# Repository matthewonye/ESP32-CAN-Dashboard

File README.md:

# ESP32-CAN-Dashboard
An embedded systems project that uses ESP32 microcontrollers and CAN bus communication to simulate, transmit, receive, and display vehicle data in real time.

The project combines C++ firmware, CAN communication, MATLAB/Simulink modeling, and custom PCB design to demonstrate hardware/software integration for automotive electronics.

# Project Overview
The system uses two ESP32 microcontrollers connected through SN65HVD230 CAN transceivers.

* Transmitter (Simulated Vehicle): Generates vehicle data, including engine RPM, speed, and coolant temperature, and transmits it over CAN.

* Receiver (Dashboard): Receives and decodes CAN messages and displays the vehicle data on a 128×64 OLED screen.

A custom PCB was designed in KiCad to integrate the dashboard ESP32, CAN interface, OLED connections, power regulation, and external CAN connections.

# Hardware Components
* 2 ESP32-WROOM-32 development boards (bench testing)

* SN65HVD230 CAN transceiver modules

* SSD1306 128×64 OLED display

* MP1584EN adjustable buck converter module (for PCB assembly)

* Custom designed PCB

* 120 Ω CAN termination resistor and jumper

* Screw terminals, headers, and supporting passive components

# Tech/Tools Used:

* Programming      |     C/C++, Arduino IDE

* Microcontrollers   |   ESP32

* Communication     |    CAN Bus, ESP32 TWAI

* PCB Design      |      KiCad

* Simulation      |     MATLAB/Simulink

* Interfaces     |       OLED

* Debugging       |     Serial Monitor, Multimeter

# System Architecture

Simulated Vehicle ESP32 → SN65HVD230 → CAN Bus → SN65HVD230 → Dashboard ESP32 → OLED Display

The transmitter generates simulated vehicle signals and packages them into CAN messages. The receiver reconstructs the transmitted values and updates the OLED display.

# CAN Communication

The system uses the ESP32's built-in TWAI controller with external SN65HVD230 transceivers.

CAN Configuration

* Bit rate: 500 kbps
* CAN message ID: 0x100
* Payload length: 5 bytes

Byte/Data

* 0 | RPM High

* 1 | RPM Low

* 2 | Vehicle Speed

* 3 | Coolant Temp

* 4 | Reserved

where RPM is encoded as a 16-bit value and reconstructed by the receiver using bitwise operations.

# [MATLAB/Simulink](https://github.com/matthewonye/ESP32-CAN-Dashboard/tree/main/Simulink)

Developed a Simulink model to simulate vehicle signals and demonstrate CAN payload encoding and decoding.

The model includes:

* Simulated RPM, speed, and coolant temperature signals
* Signal saturation and data-type conversion
* High-byte/low-byte encoding
* Byte-level payload construction
* Decoding and reconstruction of transmitted values

The Simulink model validates the data processing logic; physical CAN communication is handled by the ESP32 hardware and firmware.

# [Custom PCB Design](https://github.com/matthewonye/ESP32-CAN-Dashboard/tree/main/PCB/KiCAD/CAN_Dashboard_PCB)

Designed a multi layer PCB in KiCad to integrate the dashboard hardware into a single assembly.

PCB features:
* ESP32 DevKit footprint

* SN65HVD230 module interface

* OLED connector

* External CANH/CANL/GND connector

* Buck-converter power section

* Switchable 120 Ω CAN termination

* Power indicator LED

* Signal and power test points

* Ground copper plane

* ESP32 antenna copper keepout

# Testing and Validation
* Established CAN communication between two ESP32 development boards

* Verified message transmission and reception

* Decoded vehicle data and displayed it on the OLED

* Validated signal encoding and decoding in MATLAB/Simulink

* Completed KiCad electrical and PCB design-rule checks

# Future Additions 
* Integrate an Assembly routine for low-level data processing

* Add vehicle-data logging capabilities

* Expand dashboard visualization

* Evaluate a protected, listen-only interface for real vehicle CAN networks

# Author
Matthew Onye

Computer Engineering | University of Michigan–Dearborn

[LinkedIn](https://www.linkedin.com/in/matthew-onye-9a4964316/?isSelfProfile=true)

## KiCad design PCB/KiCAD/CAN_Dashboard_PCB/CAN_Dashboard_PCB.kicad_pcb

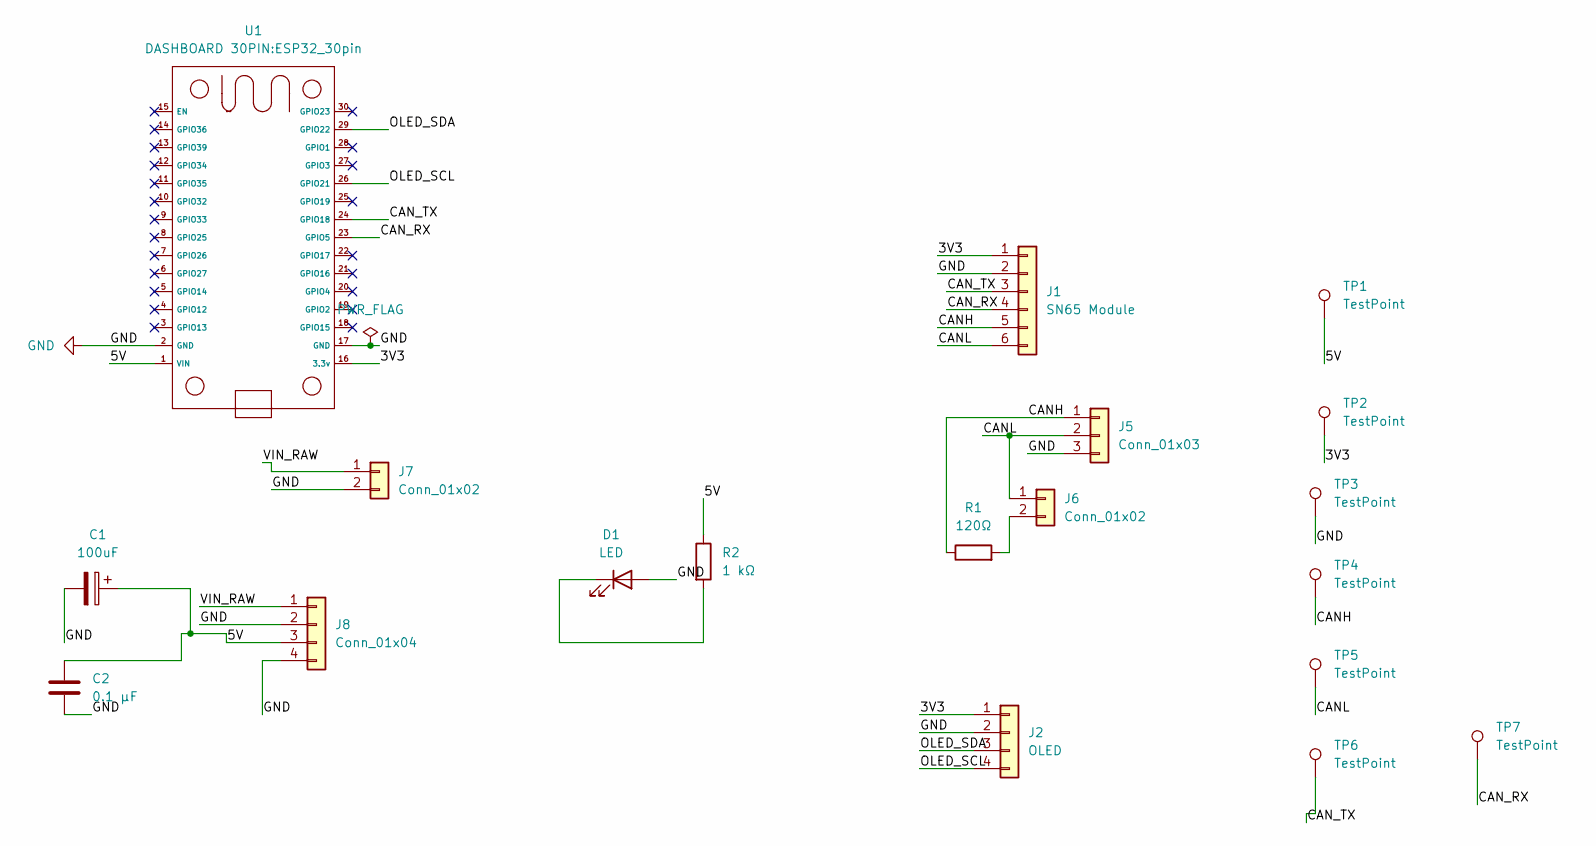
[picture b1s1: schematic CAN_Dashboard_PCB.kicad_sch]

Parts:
C1: 100uF; CP_Radial_D6.3mm_P2.50mm
C2: 0.1 µF; C_Disc_D5.0mm_W2.5mm_P5.00mm
D1: LED; LED_D5.0mm
J1: SN65 Module; PinHeader_1x06_P2.54mm_Vertical
J2: OLED; FanPinHeader_1x04_P2.54mm_Vertical
J5: Conn_01x03; TerminalBlock_Phoenix_MKDS-1,5-3-5.08_1x03_P5.08mm_Horizont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
J6: Conn_01x02; PinHeader_1x02_P2.54mm_Vertical
J7: Conn_01x02; TerminalBlock_Phoenix_MKDS-1,5-2-5.08_1x02_P5.08mm_Horizont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
J8: Conn_01x04; MP1584EN_Mini_Module
R1: 120Ω; R_Axial_DIN0207_L6.3mm_D2.5mm_P10.16mm_Horizontal
R2: 1 kΩ; R_Axial_DIN0207_L6.3mm_D2.5mm_P10.16mm_Horizontal
TP1, TP2, TP3, TP4, TP5, TP6, TP7: TestPoint; TestPoint_THTPad_D2.0mm_Drill1.0mm
U1: ESP32_30pin

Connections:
/3V3: J1.1, J2.1, TP2.1 (1_1), U1.16 (3.3v)
/5V: C1.1, C2.1, J8.3, R2.1, TP1.1 (1_1), U1.1 (VIN)
/CANH: J1.5, J5.1, R1.1, TP4.1 (1_1)
/CANL: J1.6, J5.2, J6.1, TP5.1 (1_1)
/CAN_RX: J1.4, TP7.1 (1_1), U1.23 (GPIO5)
/CAN_TX: J1.3, TP6.1 (1_1), U1.24 (GPIO18)
/OLED_SCL: J2.4, U1.26 (GPIO21)
/OLED_SDA: J2.3, U1.29 (GPIO22)
/VIN_RAW: J7.1, J8.1
GND: C1.2, C2.2, D1.2 (A), J1.2, J2.2, J5.3, J7.2, J8.2, J8.4, TP3.1 (1_1), U1.2 (GND), U1.17 (GND)
unnamed: D1.1 (K), R2.2
unnamed: J6.2, R1.2

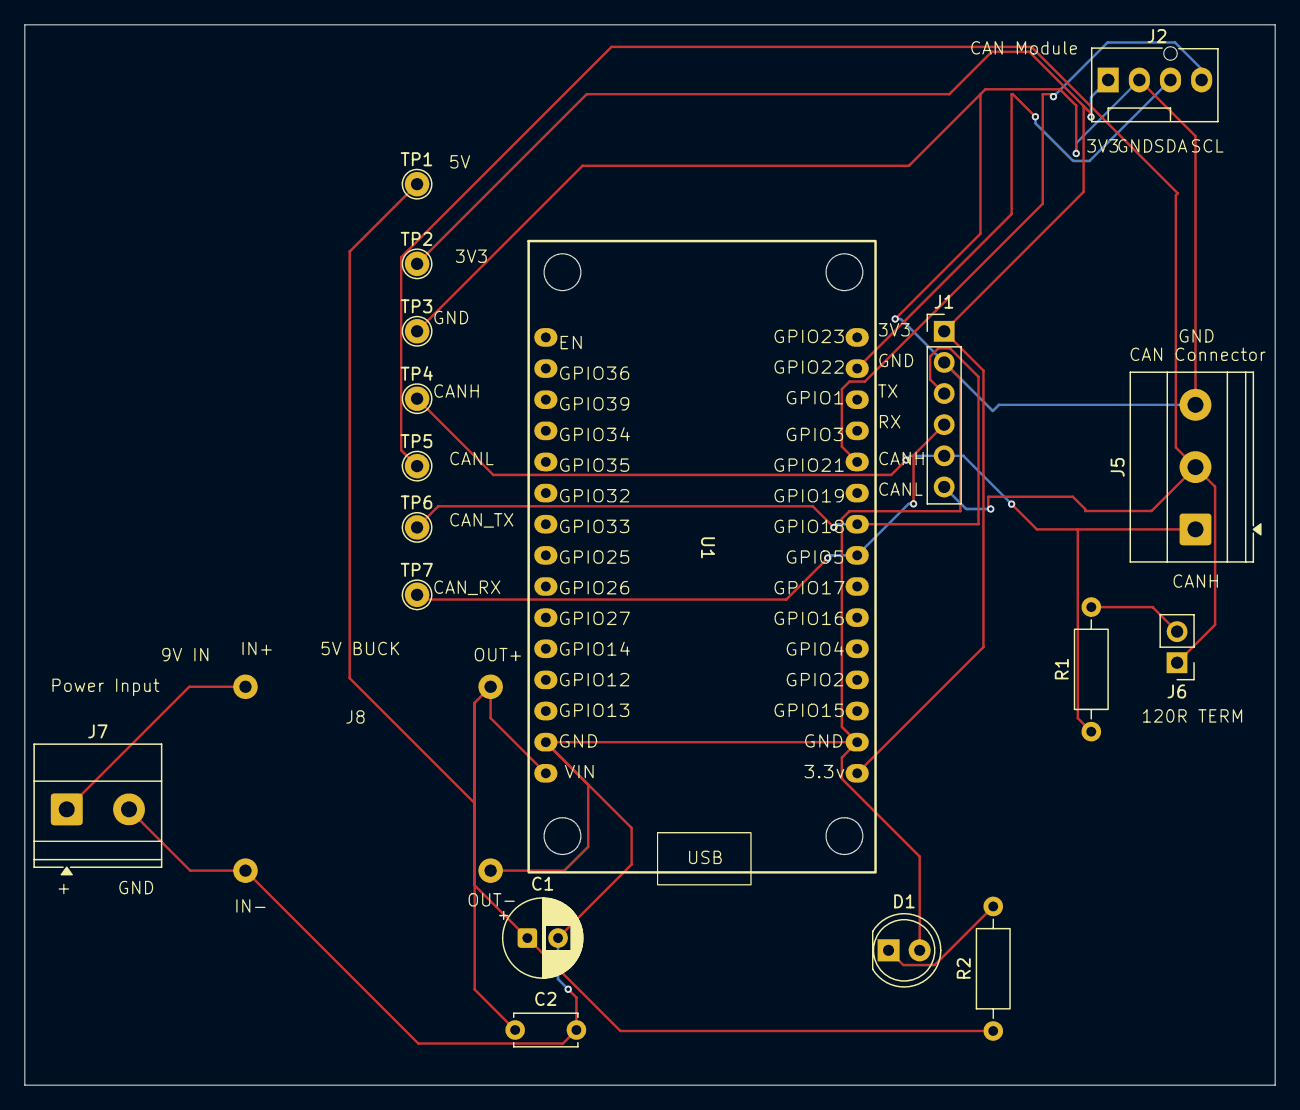
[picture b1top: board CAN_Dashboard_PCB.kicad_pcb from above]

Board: 2 copper layers, 102.0 x 86.5 mm, 19 parts (0 on the bottom side), 12 nets.
